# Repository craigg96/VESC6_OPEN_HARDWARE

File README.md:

# VESC6_OPEN_HARDWARE
Open source implementation of the vesc 6 hardware schematics published by Benjamin Vedder. Built in KiCAD and contains JLCPCB component IDs for everthing populated on the board so anyone can order their own!

## Design
* Continuous current: 70A; instantaneous current: 120A (With proper heat sinking)
* STL130N6F7 MOSFETs rated to switch up to 130A, software limits it to 120A.
* Voltage: 10V-60V(Cells: 3-13S)
* Ports: USB, CAN x2, ADC, on/off switch, SWD, Hall Sensors
* LSM6DS3 IMU
* JST-SH connectors (6pin and 4 pin)
* Holes either side of the MOSFETs allow for even clamping of a simple rectangular heatsink.

## Manufacture
* Economy PCBA maufacture can be used without placing the IMU - 5 boards approx £160GBP
* Standard PCBA manufacture with placing the IMU costs more - 5 boards approx £200GBP
* Custom board software build as well as hardware configuration files are available in the software folder.

## Testing so far...
Release 1 has been flashed and fully tested on the bench to verify current feedback, backEMF sensing, temperature sensing and IMU work as expected.
Hardware has been field tested by several months of daily use (ebike) pulling sustained power over 2kW with no issues.

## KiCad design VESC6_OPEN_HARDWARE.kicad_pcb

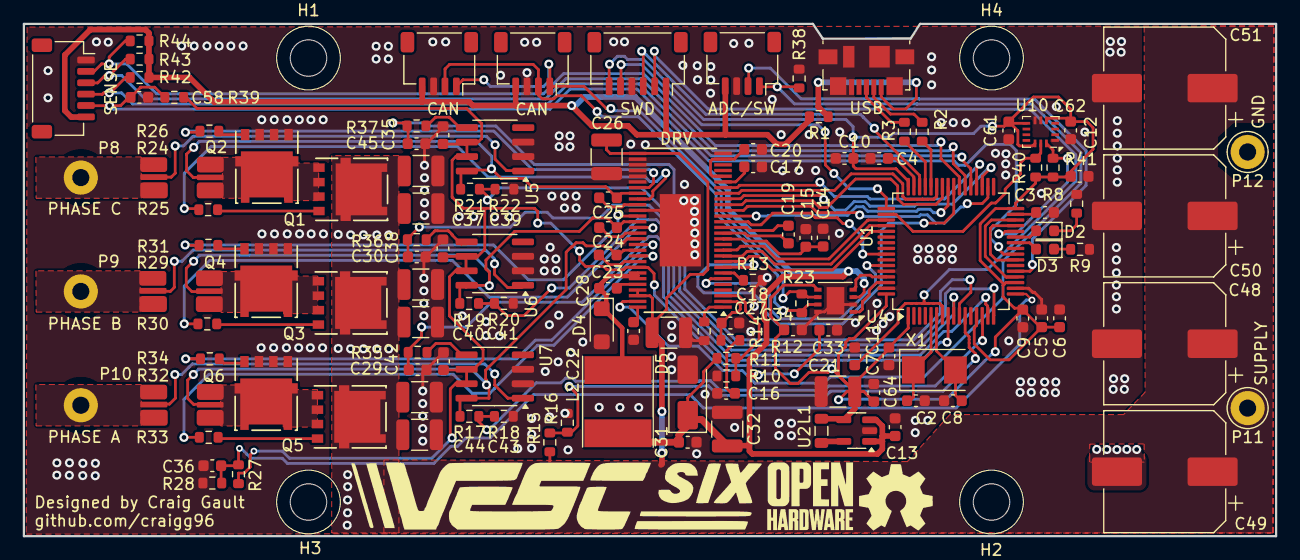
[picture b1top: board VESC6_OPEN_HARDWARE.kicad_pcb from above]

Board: 4 copper layers, 110.0 x 45.0 mm, 128 parts (0 on the bottom side), 92 nets.

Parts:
ADC/SW: ADC_SWITCH; JST_SH_SM04B-SRSS-TB_1x04-1MP_P1.00mm_Horizontal
C2, C8: 15p; C_0603_1608Metric
C3, C4, C5, C6, C9, C10, C11, C12, C13, C14, C15, C17, C20, C31, C33, C34, C35, C36, C38, C42, C64: 2.2uF; C_0603_1608Metric
C7, C28, C58, C61, C62: 100n; C_0603_1608Metric
C16: 6.8n; C_0603_1608Metric
C18: 120p; C_0603_1608Metric
C19: 22n; C_0603_1608Metric
C21, C32: 100u; C_1210_3225Metric
C22: 15n; C_0603_1608Metric
C23, C24, C25: 220n; C_0603_1608Metric
C26, C27, C37, C39, C40, C41, C43, C44: 4.7u_100v; C_1210_3225Metric
C29, C30, C45: 4.7n; C_0603_1608Metric
C48, C49, C50, C51: 220u_63v; CP_Elec_10x10.5
CAN: CAN1; JST_SH_SM04B-SRSS-TB_1x04-1MP_P1.00mm_Horizontal
CAN#2: CAN2; JST_SH_SM04B-SRSS-TB_1x04-1MP_P1.00mm_Horizontal
D2: RED; D_0603_1608Metric
D3: WHITE; D_0603_1608Metric
D4: DIODE; D_SMF
D5: TVS 5V; D_SMA
H1, H2, H3, H4: MountingHole; MountingHole_3mm
L1: 2.2u; L_0805_2012Metric
L2: 22u; L_Taiyo-Yuden_NR-60xx_HandSoldering
P8: PH_C; Pin_D1.3mm_L11.0mm_LooseFit
P9: PH_B; Pin_D1.3mm_L11.0mm_LooseFit
P10: PH_A; Pin_D1.3mm_L11.0mm_LooseFit
P11: SUPPLY; Pin_D1.3mm_L11.0mm_LooseFit
P12: GND; Pin_D1.3mm_L11.0mm_LooseFit
Q1, Q2, Q3, Q4, Q5, Q6: STL130N6F7; NVMFS5C612NL
R1: DNP; R_0603_1608Metric
R2, R3: 22R; R_0603_1608Metric
R8, R9, R23: 120R; R_0603_1608Metric
R10: 3.3k; R_0603_1608Metric
R11: 18k; R_0603_1608Metric
R12: 15k; R_0603_1608Metric
R13, R28, R38, R39: 10k; R_0603_1608Metric
R14: 220k; R_0603_1608Metric
R15, R17, R19, R21: 39k; R_0603_1608Metric
R16, R18, R20, R22, R42, R43, R44: 2k2; R_0603_1608Metric
R24, R29, R32: 0.0005R; 2512_SHUNT
R25, R26, R30, R31, R33, R34: 4.7R; R_0603_1608Metric
R27: NTC 10k; R_0603_1608Metric
R35, R36, R37: 100R; R_0603_1608Metric
R40, R41: 1k; R_0603_1608Metric
SENSE: HALL/Encoder; JST_SH_SM06B-SRSS-TB_1x06-1MP_P1.00mm_Horizontal
SWD: SWD; JST_SH_SM06B-SRSS-TB_1x06-1MP_P1.00mm_Horizontal
U1: STM32F40X_LQFP64; LQFP-64_10x10mm_P0.5mm
U2: LM3671; SOT-23-5
U3: DRV8301; HTSSOP-56-1EP_6.1x14mm_P0.5mm_EP3.61x6.35mm
U4: TJA1051TK-3; DFN-8-1EP_3x3mm_P0.65mm_EP1.55x2.4mm
U5, U6, U7: AD8418; SOIC-8_3.9x4.9mm_P1.27mm
U10: LSM6DS3TR-C; Bosch_LGA-14_3x2.5mm_P0.5mm
USB: USB_OTG; USB_Micro-B_Molex_47346-0001
X1: 8m; Crystal_SMD_5032-2Pin_5.0x3.2mm

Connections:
+5V: ADC/SW.4, C13.1, C31.1, C32.1, C33.1, CAN.4, CAN#2.4, D5.1 (K), L2.2, R1.1, R11.2, R42.2, R43.2, R44.2, SENSE.6, SWD.1, U2.1 (Vin), U2.3 (EN), U4.3 (VCC)
/CAN/CANH: CAN.2, CAN#2.2, R23.1, U4.7 (CANH)
/CAN/CANL: CAN.1, CAN#2.1, R23.2, U4.6 (CANL)
/CAN/RX: U1.61 (PB8), U4.4 (RXD)
/CAN/TX: U1.62 (PB9), U4.1 (TXD)
/DRV8301/CS: U1.40 (PC9), U3.8 (M_PWM)
/DRV8301/EN_GATE: U1.57 (PB5), U3.16 (EN_GATE)
/DRV8301/FAULT: U1.59 (PB7), U3.6 (FAULT)
/DRV8301/GH_A: R33.2, U3.47 (GH_A)
/DRV8301/GH_B: R30.2, U3.42 (GH_B)
/DRV8301/GH_C: R25.2, U3.37 (GH_C)
/DRV8301/GL_A: R34.2, U3.45 (GL_A)
/DRV8301/GL_B: R31.2, U3.40 (GL_B)
/DRV8301/GL_C: R26.2, U3.35 (GL_C)
/DRV8301/INH_A: U1.41 (PA8), U3.17 (INH_A)
/DRV8301/INH_B: U1.42 (PA9(OTG_FS_VBUS)), U3.19 (INH_B)
/DRV8301/INH_C: U1.43 (PA10), U3.21 (INH_C)
/DRV8301/INL_A: U1.34 (PB13(OTG_HS_VBUS)), U3.18 (INL_A)
/DRV8301/INL_B: U1.35 (PB14), U3.20 (INL_B)
/DRV8301/INL_C: U1.36 (PB15), U3.22 (INL_C)
/DRV8301/SCLK: U1.51 (PC10), U3.11 (OC_ADJ)
/DRV8301/SDI: U1.53 (PC12), U3.9 (M_OC)
/DRV8301/SDO: U1.52 (PC11), U3.10 (GAIN)
/DRV8301/SENS_A: R17.2, R18.2, U1.14 (PA0(ADC123_IN0/WKUP))
/DRV8301/SENS_B: R19.2, R20.2, U1.15 (PA1(ADC123_IN1))
/DRV8301/SENS_C: R21.2, R22.2, U1.16 (PA2(ADC123_IN2))
/DRV8301/SENS_SUPPLY: R15.2, R16.2, U1.11 (PC3(ADC123_IN13))
/DRV8301/SH_A: C23.1, Q5.3 (S), Q6.1 (D), R17.1, R32.1, U3.46 (SH_A), U7.8 (IN+)
/DRV8301/SH_B: C24.1, Q3.3 (S), Q4.1 (D), R19.1, R29.1, U3.41 (SH_B), U6.8 (IN+)
/DRV8301/SH_C: C25.1, Q1.3 (S), Q2.1 (D), R21.1, R24.1, U3.36 (SH_C), U5.8 (IN+)
/DRV8301/SWITCH-: ADC/SW.1, R38.1, U3.55 (EN_BUCK)
/IMU/SCL: R40.2, U1.50 (PA15(JTDI)), U10.13 (SCX)
/IMU/SDA: R41.1, U1.28 (PB2-BOOT1), U10.14 (SDX)
/power/CURR_A: C29.1, R35.2, U1.8 (PC0(ADC123_IN10))
/power/CURR_B: C30.1, R36.2, U1.9 (PC1(ADC123_IN11))
/power/CURR_C: C45.1, R37.2, U1.10 (PC2(ADC123_IN12))
/power/C_A: R35.1, U7.5 (OUT)
/power/C_B: R36.1, U6.5 (OUT)
/power/C_C: R37.1, U5.5 (OUT)
/power/TEMP: C36.1, R27.2, R28.1, U1.17 (PA3(ADC123_IN3))
/stm32f40x/HALL_1: R42.1, SENSE.4, U1.37 (PC6)
/stm32f40x/HALL_2: R43.1, SENSE.3, U1.38 (PC7)
/stm32f40x/HALL_3: R44.1, SENSE.2, U1.39 (PC8)
/stm32f40x/LED_GREEN: D3.2 (A), U1.26 (PB0(ADC12_IN8))
/stm32f40x/LED_RED: D2.2 (A), U1.27 (PB1(ADC12_IN9))
/stm32f40x/NRST: C7.1, SWD.2, U1.7 (NRST)
/stm32f40x/RX_SDA_NSS: U1.20 (PA4(ADC12_IN4/DAC1_OUT)), U1.30 (PB11)
/stm32f40x/SCK_ADC_EXT: ADC/SW.2, U1.21 (PA5(ADC12_IN5/DAC2_OUT))
/stm32f40x/SWCLK: SWD.5, U1.49 (PA14(JTCK-SWCLK))
/stm32f40x/SWDIO: SWD.3, U1.46 (PA13(JTMS-SWDIO))
/stm32f40x/TEMP_MOTOR: C58.2, R39.2, SENSE.5, U1.24 (PC4(ADC12_IN14))
/stm32f40x/TX_SCL_MOSI: U1.23 (PA7(ADC12_IN7)), U1.29 (PB10)
/stm32f40x/USB_DM: R2.1, U1.44 (PA11)
/stm32f40x/USB_DP: R3.1, U1.45 (PA12)
GND: ADC/SW.3, C2.1, C3.1, C4.1, C5.2, C6.2, C7.2, C8.1, C9.2, C10.2, C11.2, C12.2, C13.2, C14.2, C15.2, C16.1, C17.2, C18.1, C20.2, C21.2, C22.2, C26.2, C27.2, C29.2, C30.2, C31.2, C32.2, C33.2, C34.2, C35.2, C36.2, C37.2, C38.2, C39.2, C40.2, C41.2, C42.2, C43.2, C44.2, C45.2, C48.2, C49.2, C50.2, C51.2, C58.1, C61.1, C62.1, C64.2, CAN.3, CAN#2.3, D4.2 (A), D5.2 (A), P12.1, Q2.3 (S), Q4.3 (S), Q6.3 (S), R8.2, R9.2, R10.1, R13.2, R14.1, R16.1, R18.1, R20.1, R22.1, R28.2, R38.2, SENSE.1, SWD.4, U1.12 (VSSA), U1.18 (VSS), U1.60 (BOOT0(VPP)), U1.63 (VSS), U2.2 (GND), U3.28 (AGND), U3.30 (SP2), U3.31 (SN2), U3.32 (SP1), U3.33 (SN1), U3.34 (SL_C), U3.39 (SL_B), U3.44 (SL_A), U3.57 (GND(POWER_PAD)), U4.2 (GND), U4.8 (S), U4.9 (GND), U5.2 (GND), U5.3 (REF2), U6.2 (GND), U6.3 (REF2), U7.2 (GND), U7.3 (REF2), U10.1 (SDO), U10.6 (GNDIO), U10.7 (GND), USB.5 (GND), USB.6 (Shield)
unnamed: C16.2, R12.1
unnamed: D2.1 (K), R8.1
unnamed: D3.1 (K), R9.1
unnamed: C28.1, D4.1 (K), L2.1, U3.50 (PH), U3.51 (PH)
unnamed: R3.2, USB.3 (D+)
unnamed: R2.2, USB.2 (D-)
unnamed: R1.2, USB.1 (VBUS)
unnamed: P8.1, R24.2, U5.1 (IN-)
unnamed: P9.1, R29.2, U6.1 (IN-)
unnamed: P10.1, R32.2, U7.1 (IN-)
unnamed: Q1.2 (G), R25.1
unnamed: Q2.2 (G), R26.1
unnamed: Q3.2 (G), R30.1
unnamed: Q4.2 (G), R31.1
unnamed: Q5.2 (G), R33.1
unnamed: Q6.2 (G), R34.1
unnamed: C2.2, U1.5 (PH0-OSC_IN), X1.1
unnamed: C8.2, U1.6 (PH1-OSC_OUT), X1.2
unnamed: C3.2, U1.31 (VCAP1)
unnamed: C4.2, U1.47 (VCAP2)
unnamed: L1.1, U2.5 (SW)
unnamed: C20.1, U3.24 (REF), U3.27 (AVDD)
unnamed: C23.2, U3.48 (BST_A)
unnamed: C24.2, U3.43 (BST_B)
unnamed: C28.2, U3.52 (BST_BK)
unnamed: C25.2, U3.38 (BST_C)
unnamed: C18.2, R12.2, U3.2 (COMP)
unnamed: C19.1, U3.14 (CP1)
unnamed: C19.2, U3.15 (CP2)
unnamed: R13.1, U3.7 (DTC)
unnamed: C17.1, U3.23 (DVDD)
unnamed: C14.1, C15.1, U3.13 (GVDD)
unnamed: R14.2, U3.1 (RT_CLK)
unnamed: C22.1, U3.56 (SS_TR)
unnamed: R10.2, R11.1, U3.3 (VSENSE)
SUPPLY: C26.1, C27.1, C37.1, C39.1, C40.1, C41.1, C43.1, C44.1, C48.1, C49.1, C50.1, C51.1, P11.1, Q1.1 (D), Q3.1 (D), Q5.1 (D), R15.1, U3.29 (PVDD1), U3.53 (PVDD2), U3.54 (PVDD2)
VCC: C5.1, C6.1, C9.1, C10.1, C11.1, C12.1, C21.1, C34.1, C35.1, C38.1, C42.1, C61.2, C62.2, C64.1, L1.2, R27.1, R39.1, R40.1, R41.2, SWD.6, U1.1 (VBAT), U1.13 (VDDA), U1.19 (VDD), U1.32 (VDD), U1.48 (VDD), U1.64 (VDD), U2.4 (FB), U3.49 (BIAS), U4.5 (VIO), U5.6 (VS), U5.7 (REF1), U6.6 (VS), U6.7 (REF1), U7.6 (VS), U7.7 (REF1), U10.5 (VDDIO), U10.8 (VDD), U10.12 (CSB)

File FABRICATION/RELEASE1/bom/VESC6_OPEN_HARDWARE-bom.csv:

Designator,JLCPCB Part #,Qty,Value
"C2,C8",C1644,2,15p
"C3,C4,C5,C6,C9,C10,C11,C12,C13,C14,C15,C17,C20,C31,C33,C34,C35,C36,C38,C42,C64",C23630,21,2.2uF
"C7,C28,C58,C61,C62",C14663,5,100n
C16,C1631,1,6.8n
C18,C107035,1,120p
C19,C21122,1,22n
"C21,C32",C16133,2,100u
C22,C1596,1,15n
"C23,C24,C25",C21120,3,220n
"C26,C27,C37,C39,C40,C41,C43,C44",C385987,8,4.7u_100v
"C29,C30,C45",C53987,3,4.7n
"C48,C49,C50,C51",C7471900,4,220u_63v
D2,C2286,1,RED
D3,C2290,1,WHITE
D4,C2923951,1,DIODE
D5,C129544,1,TVS 5V
"H1,H2,H3,H4",,4,MountingHole
L1,C383398,1,2.2u
L2,C266430,1,22u
P1,C132560,1,USB_OTG
"P2,P5,P6",C23390337,1,4PINCONN
"P3,P4",C160405,1,6PINCONN
P8,,1,PH_C
P9,,1,PH_B
P10,,1,PH_A
P11,,1,SUPPLY
P12,,1,GND
"Q1,Q2,Q3,Q4,Q5,Q6",C501008,6,STL130N6F7
R1,,1,DNP
"R2,R3",C23345,2,22R
"R8,R9,R23",C22787,3,120R
R10,C22978,1,3.3k
R11,C25810,1,18k
R12,C22809,1,15k
"R13,R28,R38,R39",C25804,4,10k
R14,C22961,1,220k
"R15,R17,R19,R21",C23153,4,39k
"R16,R18,R20,R22,R42,R43,R44",C4190,7,2k2
"R24,R29,R32",C469426,3,0.0005R
"R25,R26,R30,R31,R33,R34",C23164,6,4.7R
R27,C76589,1,NTC 10k
"R35,R36,R37",C22775,3,100R
"R40,R41",C21190,2,1k
U1,C15742,1,STM32F40X_LQFP64
U2,C477918,1,LM3671
U3,C98969,1,DRV8301
U4,C124020,1,TJA1051TK-3
"U5,U6,U7",C495342,3,AD8418
U10,C967633,1,LSM6DS3TR-C
X1,C115962,1,8m

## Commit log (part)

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2025-03-27 init
2025-03-29 started power stage
2025-03-29 power stage complete
2025-04-02 DRV8301 Stage Complete
2025-04-13 Begun wiring main MCU
2025-05-29 more routing connectors and caps
2025-06-03 More routing, positioning and SMT USB
2025-06-04 Routing cleanup
2025-06-05 double CAN ports
2025-06-09 Adjusted connectors and routing
2025-06-10 Board resized and changed usb port
2025-06-11 changed connectors, needs final routing and drc
2025-06-18 Finished routing
2025-06-18 Finished traces, DRC Passed, Grounding needs revised
2025-06-23 mounting holes, more grounding and routing
2025-09-07 drc clear, added images
2025-09-14 Release
2025-09-14 Release1
2025-10-30 publish
2025-10-30 Fix image filename case in README.md
2025-10-30 Update README with Release 1 testing details
    Added information about Release 1 testing and future firmware updates.
